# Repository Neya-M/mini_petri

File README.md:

# Mini Petri

Mini Petri is a device that simulates Conway's game of life. I got this idea during a particularly boring class when I wanted something satisfying to look at.

### Highlights

- runs on a Xiao RP2040 and 3 AA batteries
- 8x8 led dot matrix to give enough space for your life to grow
- 9 buttons to easily edit and play simulations 
- portable and pocket sized (8x13x5 cm)

Here is a banana for scale.

## Build your own

Want a Mini Petri? Download the files in the "build" folder. Order the board with gerbers.zip. The case has 3d models in 2 different formats, STL and STEP. Put in the pushers on the underside of the lid and add the keycaps from the top. Use screws to attach the lid to the case. Load main.py onto the Xiao. That's it :)

I will add a more detailed assembly guide once I build it myself. 

## How to use

First, insert batteries and turn it on with the switch.

There are 9 buttons in a 3x3 arrangement for editing the starting positions and playing the simulation.

## Conway's game of life

Conway's game of life is a simulation that uses a simple set of rules to create interesting patterns.

The rules:

each cell has 9 neighbors. A filled in or lit up cell is alive (depending on what you are using to simulate it).

each generation, cells are born and die based on their neighbors. 

A living cell with less than 2 living neighbors dies the next generation. If it has 2-3 living neighbors, it survives. If it has more than 3 living neighbors, it dies, as if by overpopulation.

A dead cell can be born if it has exactly 3 living neighbors, as if by reproduction.

With time, you can create really interesting structures such as "spaceships" that glide on indefinetly, "still life" structures where cells are never born and die, and "wires" that can transfer signals in the form of cells.

## Wiring

## Other

find the onshape file here: https://cad.onshape.com/documents/10df214650d10753392c4f94/w/a985103637e720fab81ebfaa/e/7306bce063d86ed0c220e238

Zine:

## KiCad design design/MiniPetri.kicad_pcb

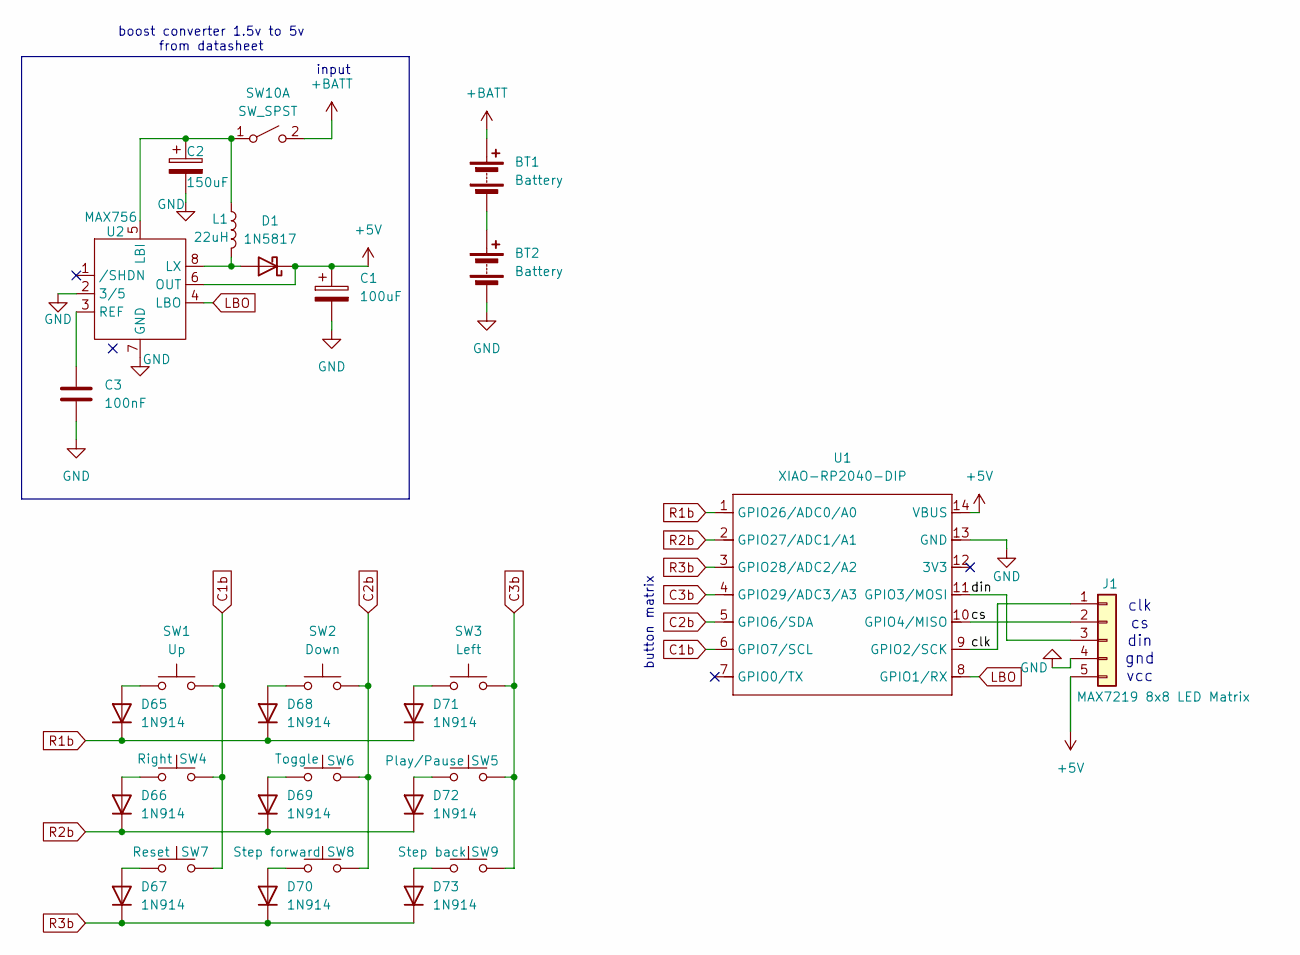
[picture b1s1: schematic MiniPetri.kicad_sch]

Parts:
BT1: Battery; BatteryHolder_Keystone_2460_1xAA
BT2: Battery; BatteryHolder_Keystone_2462_2xAA
C1: 100uF; CP_Radial_D5.0mm_P2.50mm
C2: 150uF; CP_Radial_D5.0mm_P2.50mm
C3: 100nF; C_Disc_D12.5mm_W5.0mm_P10.00mm
D1: 1N5817; D_DO-41_SOD81_P10.16mm_Horizontal
D65, D66, D67, D68, D69, D70, D71, D72, D73: 1N914; D_DO-35_SOD27_P7.62mm_Horizontal
J1: MAX7219 8x8 LED Matrix
L1: 22uH; L_10.4x10.4_H4.8
SW1: Up; SW_PUSH_6mm
SW2: Down; SW_PUSH_6mm
SW3: Left; SW_PUSH_6mm
SW4: Right; SW_PUSH_6mm
SW5: Play/Pause; SW_PUSH_6mm
SW6: Toggle; SW_PUSH_6mm
SW7: Reset; SW_PUSH_6mm
SW8: Step forward; SW_PUSH_6mm
SW9: Step back; SW_PUSH_6mm
SW10: SW_SPST; SW_DIP_SPSTx01_Slide_9.78x4.72mm_W7.62mm_P2.54mm
U1: XIAO-RP2040-DIP
U2: MAX756; SOIC-8_3.9x4.9mm_P1.27mm

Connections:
+5V: C1.1, D1.1 (K), J1.5, U1.14 (VBUS), U2.6 (OUT)
+BATT: BT1.1 (+), SW10.2 (B)
/clk: J1.1, U1.9 (GPIO2/SCK)
/cs: J1.2, U1.10 (GPIO4/MISO)
/din: J1.3, U1.11 (GPIO3/MOSI)
C1b: SW1.2, SW4.2, SW7.2, U1.6 (GPIO7/SCL)
C2b: SW2.2, SW6.2, SW8.2, U1.5 (GPIO6/SDA)
C3b: SW3.2, SW5.2, SW9.2, U1.4 (GPIO29/ADC3/A3)
GND: BT2.2 (-), C1.2, C2.2, C3.2, J1.4, U1.13 (GND), U2.2 (3/5), U2.7 (GND)
LBO: U1.8 (GPIO1/RX), U2.4 (LBO)
unnamed: BT1.2 (-), BT2.1 (+)
unnamed: D1.2 (A), L1.2, U2.8 (LX)
unnamed: D65.2 (A), SW1.1
unnamed: D66.2 (A), SW4.1
unnamed: D67.2 (A), SW7.1
unnamed: D68.2 (A), SW2.1
unnamed: D69.2 (A), SW6.1
unnamed: D70.2 (A), SW8.1
unnamed: D71.2 (A), SW3.1
unnamed: D72.2 (A), SW5.1
unnamed: D73.2 (A), SW9.1
unnamed: C2.1, L1.1, SW10.1 (A), U2.5 (LBI)
unnamed: C3.1, U2.3 (REF)
R1b: D65.1 (K), D68.1 (K), D71.1 (K), U1.1 (GPIO26/ADC0/A0)
R2b: D66.1 (K), D69.1 (K), D72.1 (K), U1.2 (GPIO27/ADC1/A1)
R3b: D67.1 (K), D70.1 (K), D73.1 (K), U1.3 (GPIO28/ADC2/A2)

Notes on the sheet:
boost converter 1.5v to 5v from datasheet
input
button matrix
clk cs din gnd vcc

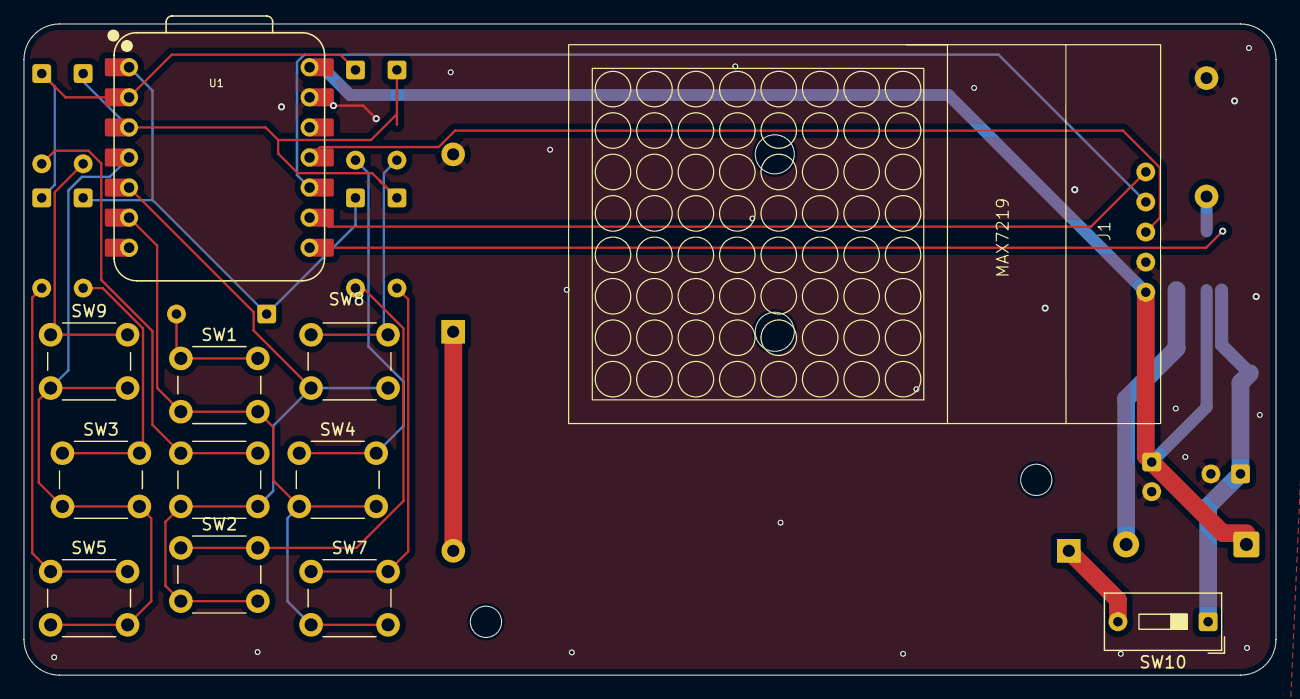
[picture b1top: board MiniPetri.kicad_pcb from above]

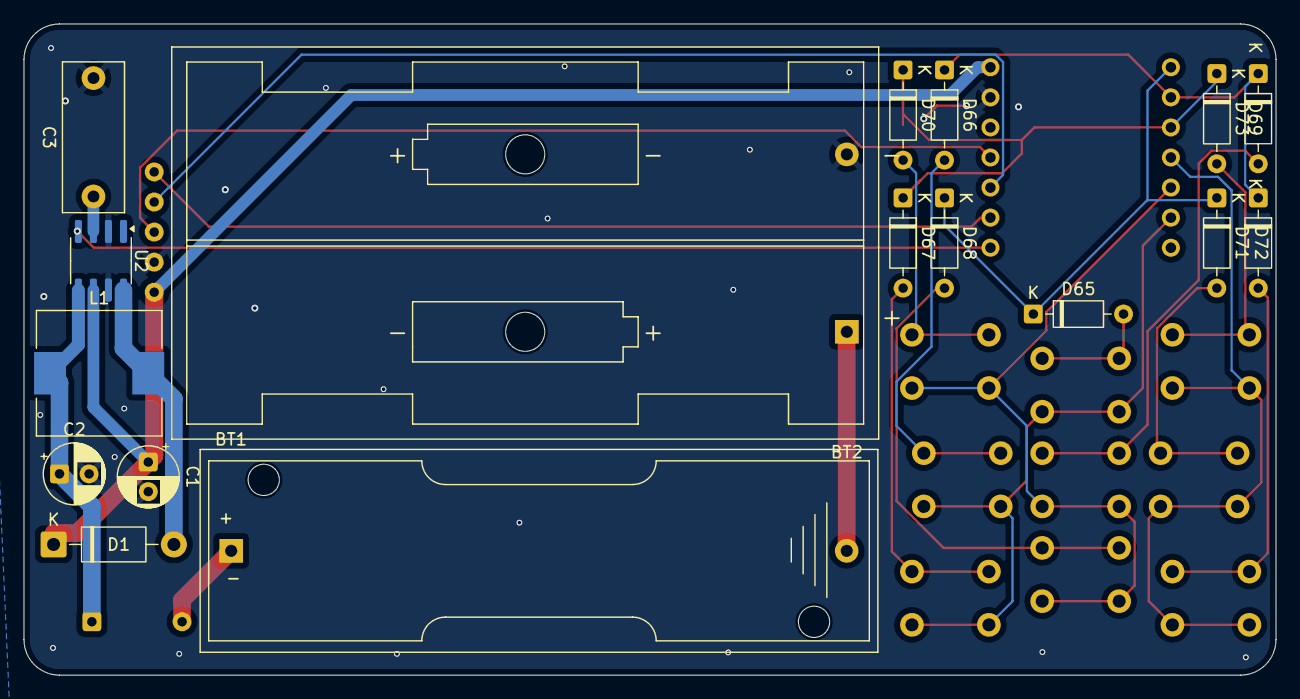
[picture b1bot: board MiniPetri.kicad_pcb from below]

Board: 2 copper layers, 105.8 x 55.0 mm, 29 parts (17 on the bottom side), 26 nets.

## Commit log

2026-06-12 init
2026-06-12 add images to readme
2026-06-13 finish up
2026-06-16 add firmware
2026-06-16 small fix
2026-06-18 another last minute fix
2026-06-19 reorganize imgs
2026-06-26 make case nicer
